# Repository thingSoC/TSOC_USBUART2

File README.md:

# TSOC_USBUART2

The thingSoC USBUART2 Base board incorporates a Cypress CY7C65215 Dual Channel USB Bridge, that supports UART, I2C, SPI, and JTAG interfaces in a thingSoC format.

The thingSoC USBUART2 Base board has two USB bridge channels, which can be programmed to be either UART, I2C, SPI, JTAG, or Capacitance Sensing (buttons/sliders) Human Input devices.

USB Bridge One (Port 1) is connected to an FTDI pinout compatible programming connector, while USB Bridge Two (Port 2) is connected to the thingSoC standard UART channel.

Port1 can be used to program a target microprocessor, at the same time Port2 is used for another purpose (i.e. debug channel, USB to RS-485 bridge, etc).  

It's like having two (2) FTDI adapters in One!

[ 
TSOC_USBUART2](https://github.com/thingSoC/TSOC_USBUART2)

The thingSoC Digital Programming Connector (DPC) is backward compatible with 
the industry standard six (6) pin "FTDI" pinout USB to Serial Adapter pinout.
However, the thingSoC Digital Programming Connector (DPC) includes 
two(2) extra pins (RTS & DEBUG) for extended device programming, 
such as "NodeMCU types" which use the RTS signal as a programming Enable,
and the DTR signal as a programming Reset.

---------------------------------------
## Use it as a Programming Dongle

[ 
TSOC_USBUART2 to FTDI Six (6) Pin : Programming an Arduino Pro](https://github.com/thingSoC/TSOC_USBUART2)

[ 
Programming a TSOC_NeoLED Board](https://github.com/thingSoC/TSOC_USBUART2)

[ 
Programming a TSOC_RS485 Board](https://github.com/thingSoC/TSOC_USBUART2)

---------------------------------------
## Use it as a Protocol Adapter

[ 
USB to WiFi Adapter](https://github.com/thingSoC/TSOC_USBUART2)

[ 
USB to RS-485 Adapter](https://github.com/thingSoC/TSOC_USBUART2)

[ 
USB to RS-232 Adapter](https://github.com/thingSoC/TSOC_USBUART2)

---------------------------------------
## TSOC_USBUART2 Model Images

[ 
TSOC_USBUART2](https://github.com/thingSoC/TSOC_USBUART2)

[ 
TSOC_USBUART2](https://github.com/thingSoC/TSOC_USBUART2)

---------------------------------------

## TSOC_USBUART2 Status <a name="TSOC_USBUART2_status"/>

Revision 1.0 - New Layout with Dual USB to UART device

Revision 2.0 - New PCB Outline, update to thingSoC Revision 2.0 

Revision 4.0 - New DPC connector, fix spacing.

Revision 4.1 - Update silkscreen, add more legends

---------------------------------------

## TSOC_USBUART2 Documentation Index <a name="TSOC_USBUART2_documentation_index"/>

[TSOC_USBUART2 Project](https://github.com/thingSoC/TSOC_USBUART2/)

[TSOC_USBUART2 Hardware](https://github.com/thingSoC/TSOC_USBUART2/tree/master/TSOC_USBUART2/hardware)

---------------------------------------

## thingSoC Documentation Index <a name="thingSoC_documentation_index"/>

[thingSoC Organization Website](http://thingSoC.github.io)

[thingSoC FAQ - Frequently Asked Questions](http://thingsoc.github.io/support/faq.html)

---------------------------------------

[ 
*thingSoC*](http://thingsoc.github.io)

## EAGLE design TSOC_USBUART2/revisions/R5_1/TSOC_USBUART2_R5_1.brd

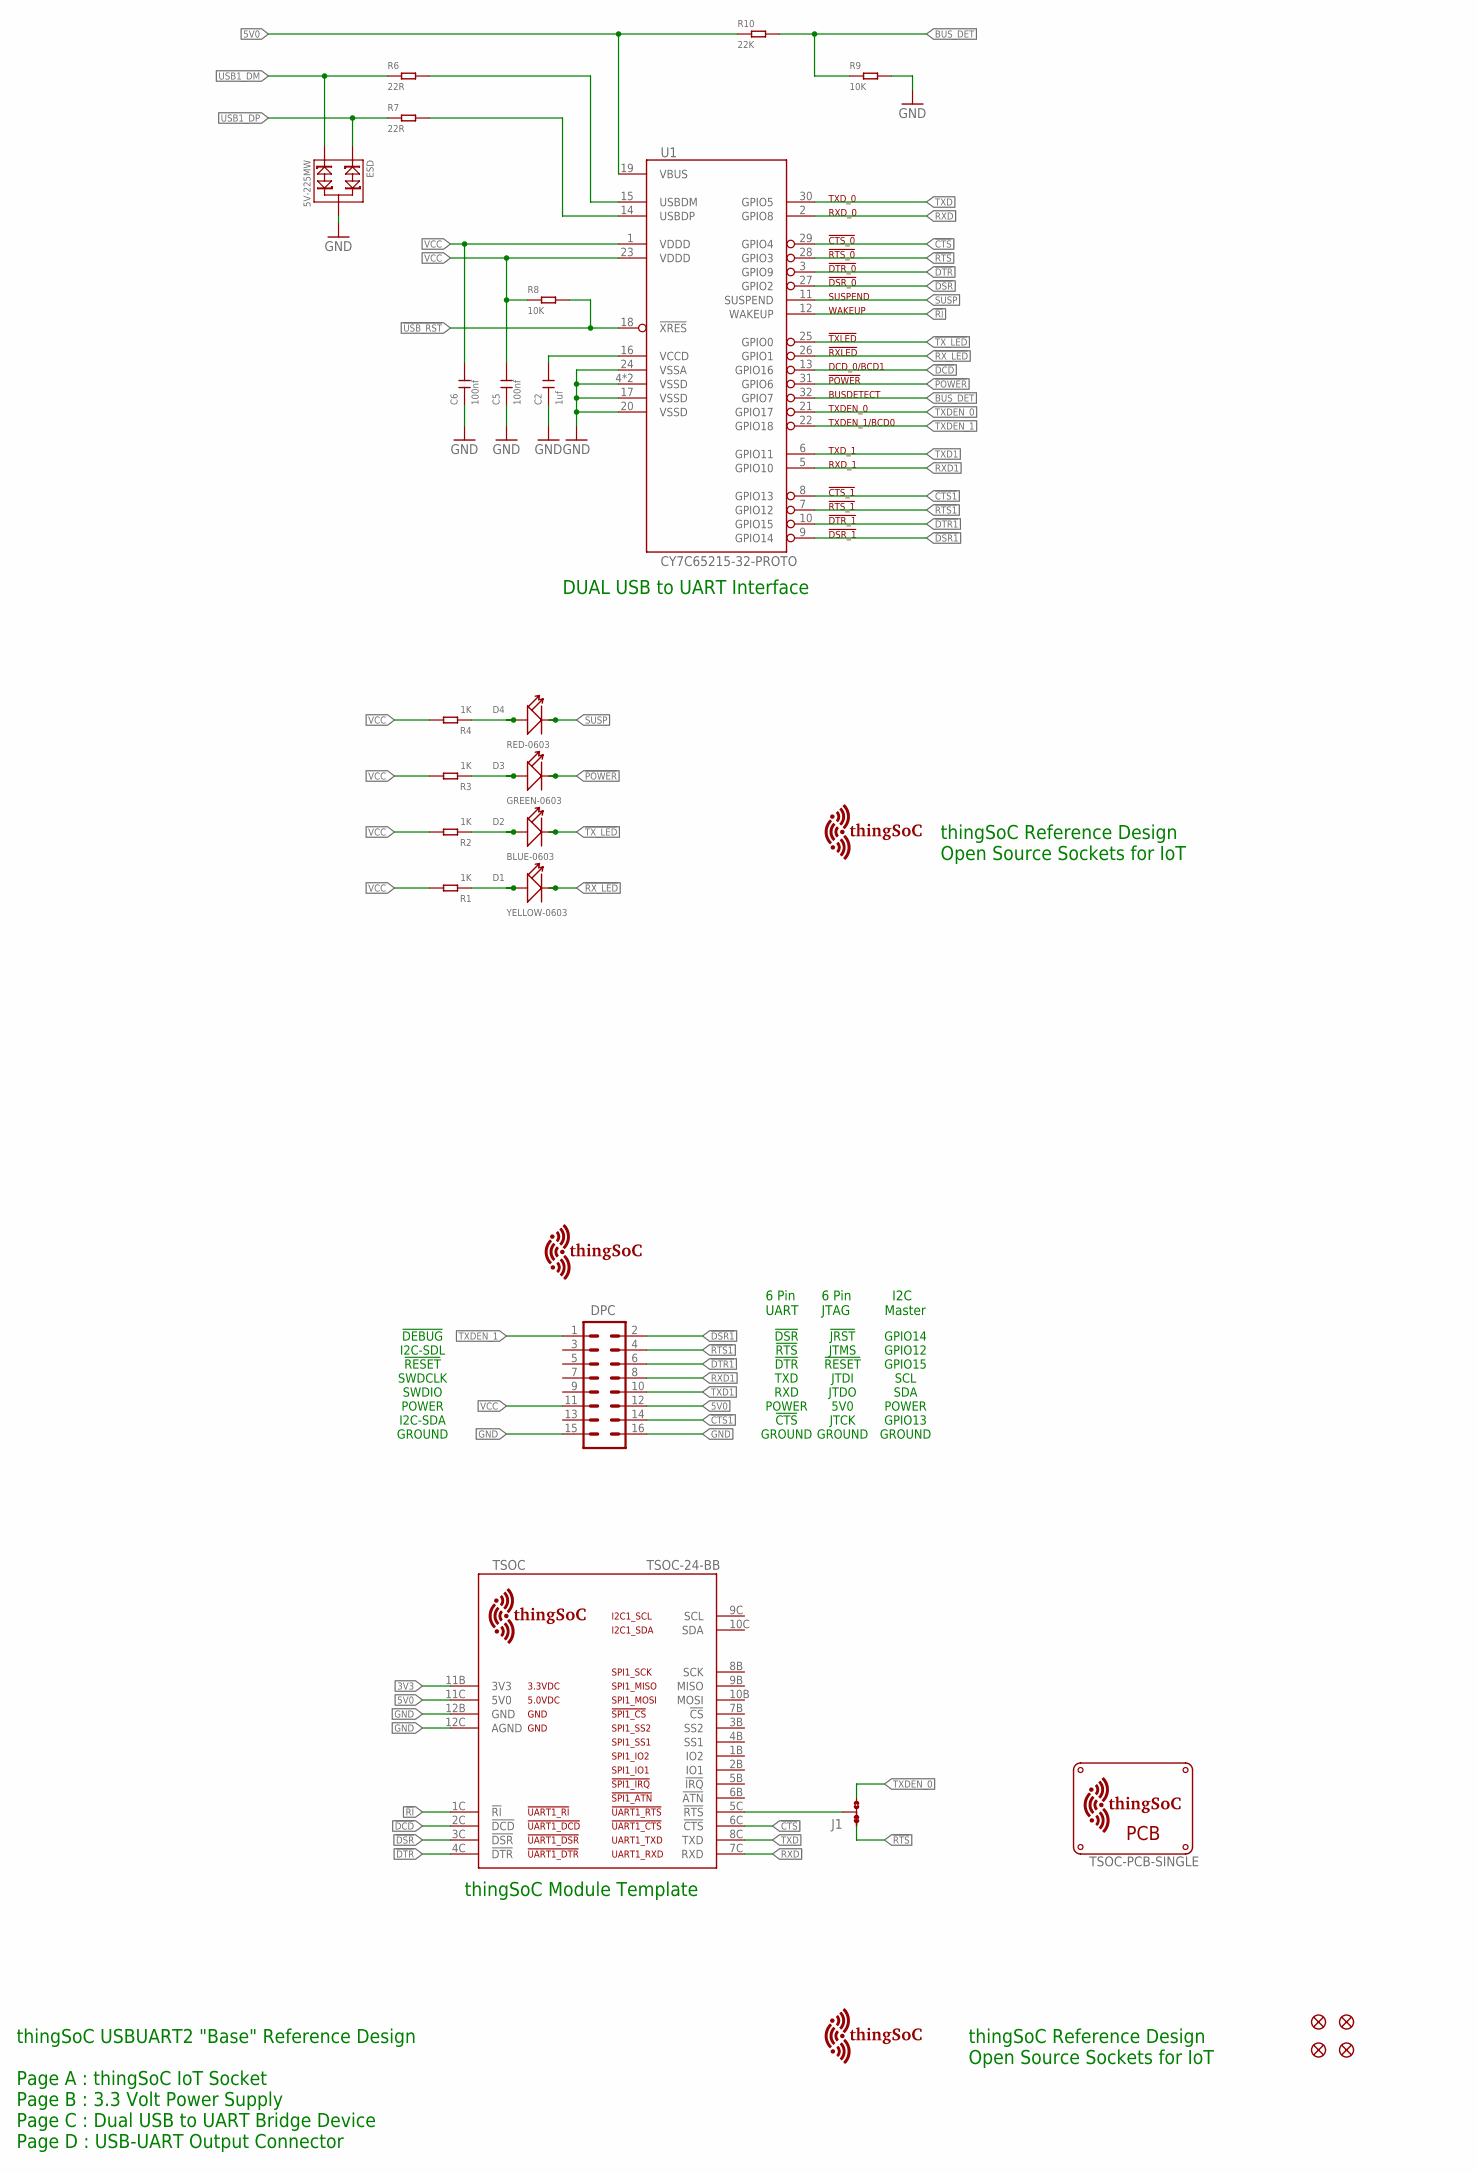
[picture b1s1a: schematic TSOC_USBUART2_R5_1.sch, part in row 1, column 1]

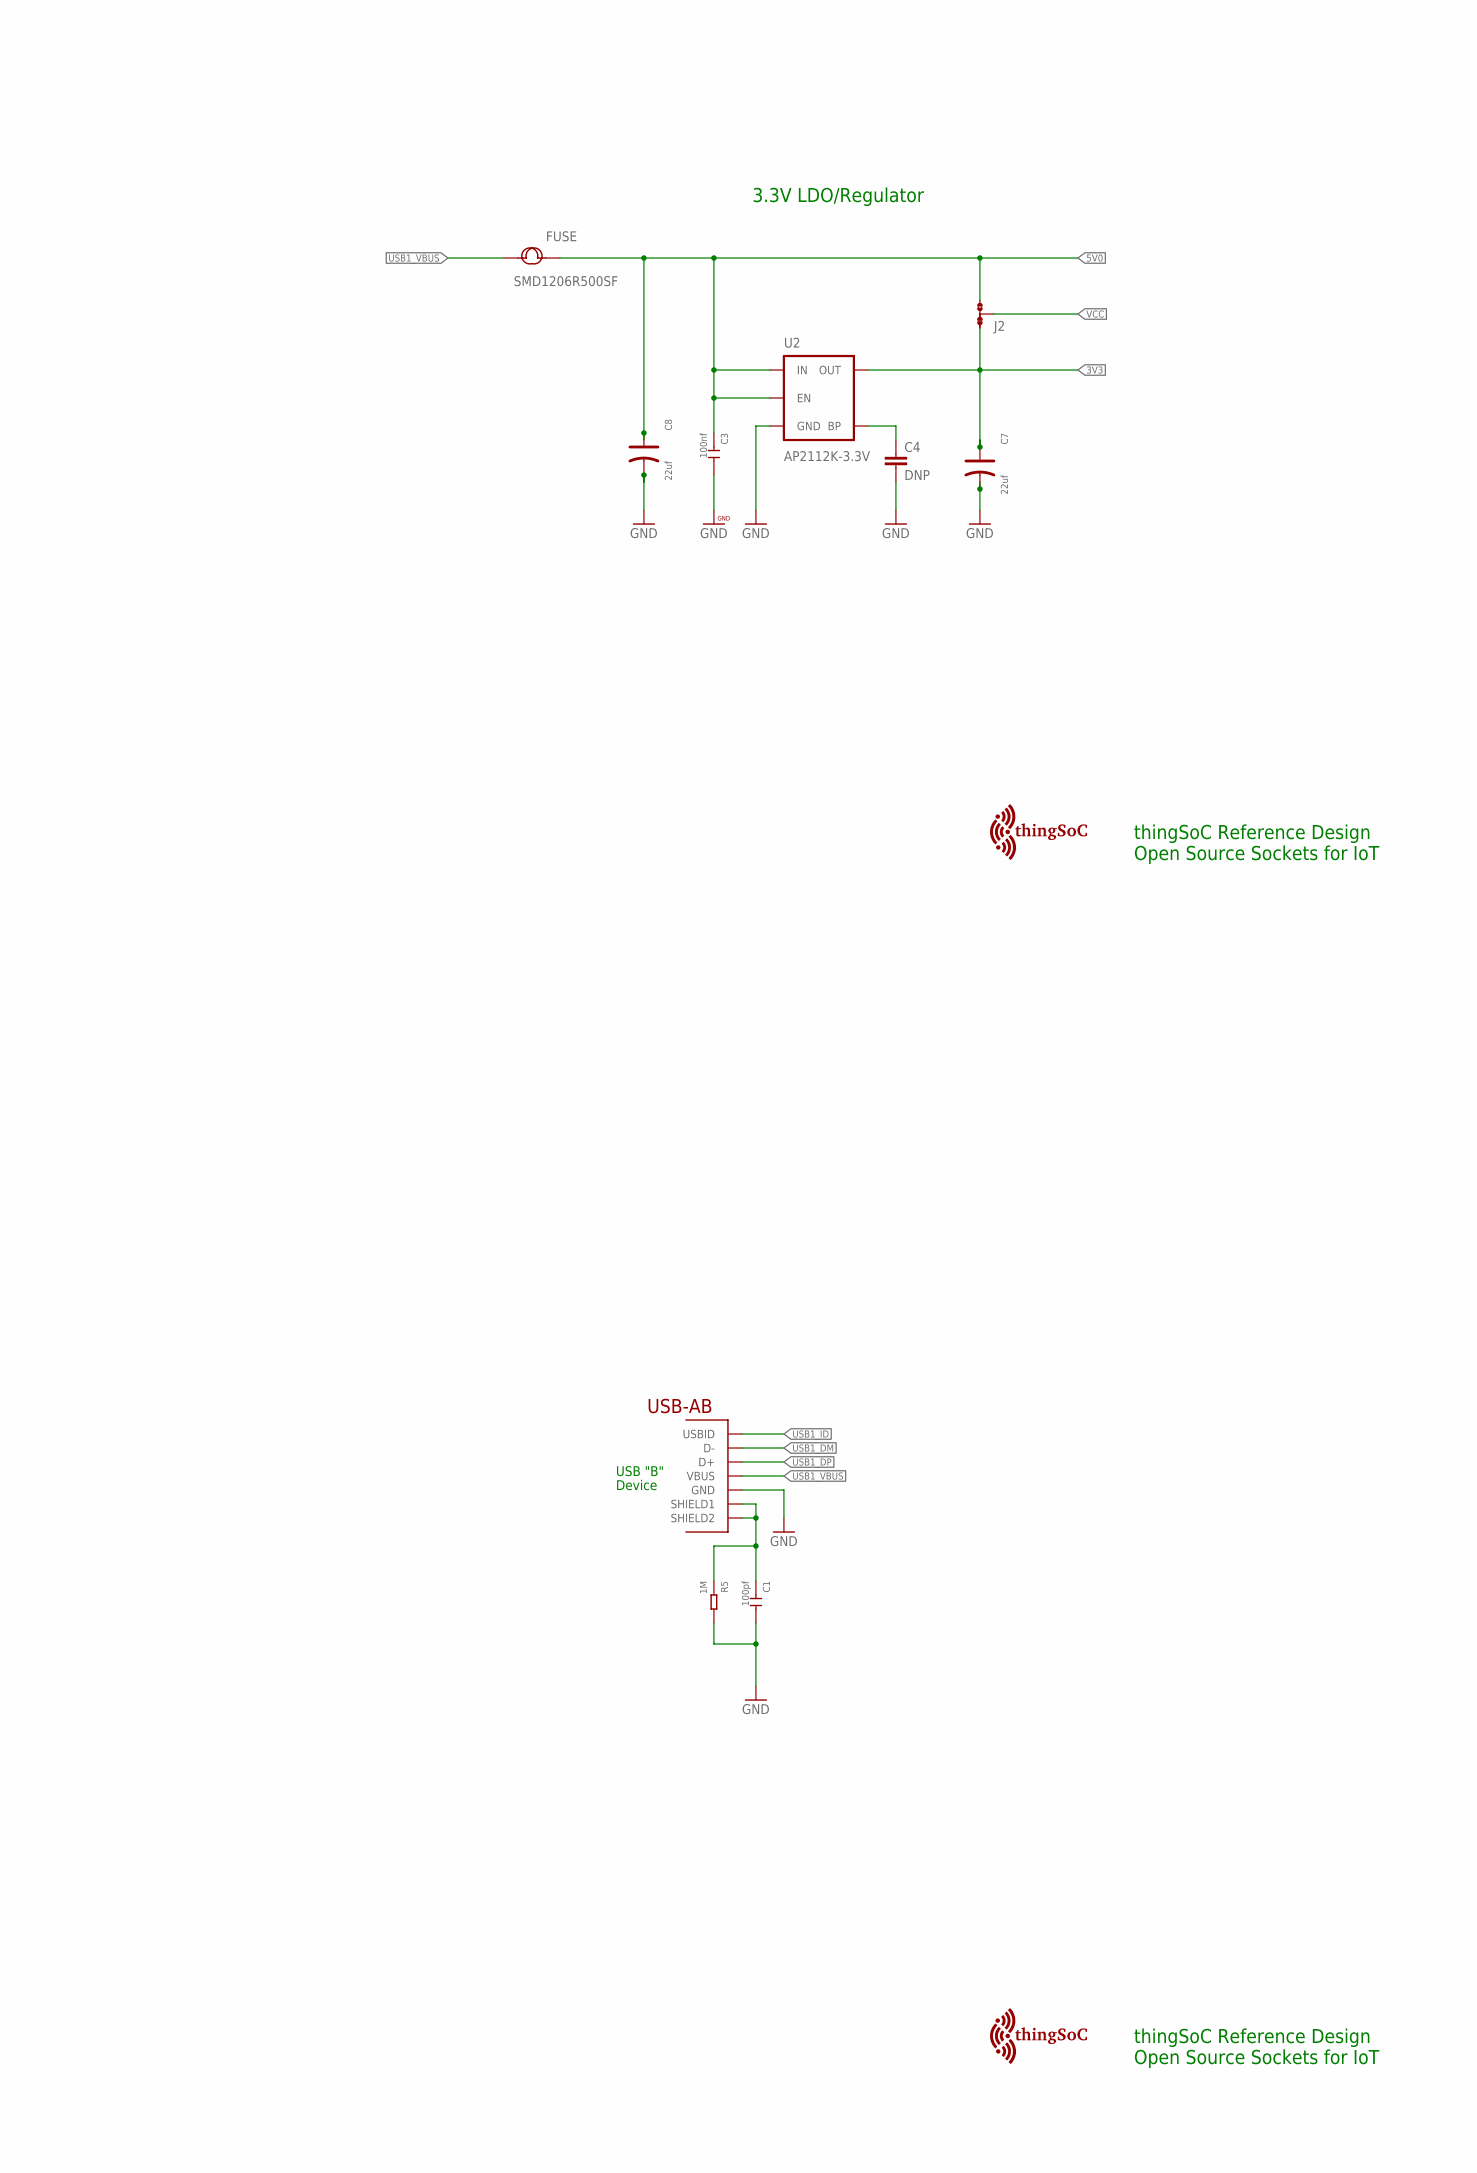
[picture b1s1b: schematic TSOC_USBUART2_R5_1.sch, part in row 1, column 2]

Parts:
$$U$2: TSOC-LOGO; TSOC-LOGO-BLANK
C1: 100pf; C0603
C2: 1uf; C0603
C3, C5, C6: 100nf; C0603
C4: DNP; EIA-0603
C7, C8: 22uf; AVX-A
D1: YELLOW-0603; LED-0603
D2: BLUE-0603; LED-0603
D3: GREEN-0603; LED-0603
D4: RED-0603; LED-0603
DPC: M08X2; 2X8
ESD: 5V-225MW; SOT-23
FID1, FID2, FID3, FID4: FIDUCIALUFIDUCIAL; MICRO-FIDUCIAL
FUSE: SMD1206R500SF; F1206
J1, J2: JMP-3-1_2
R1, R2, R3, R4: 1K; R0603
R5: 1M; R0603
R6, R7: 22R; R0603
R8, R9: 10K; R0603
R10: 22K; R0603
TSOC: TSOC-24-BB; TSOC-BB-S24
U1: CY7C65215-32-PROTO; QFN32-PROTO
U2: AP2112K-3.3V; SOT23-5
U$1, U$3: TSOC-LOGO; TSOC-LOGO-BLANK
U$4: TSOC-PCB-SINGLE; TSOC-BB-BRD-DIM
U$7: TSOC-LOGO-SMALL; TSOC-LOGO-SML
U$100: TSOC-LOGO-LRG
USB: USB_AB; USB-AB-MICRO-SMD

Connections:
3V3: C7.+, J2.1, TSOC.11B (3V3), U2.5 (OUT)
5V0: C3.1, C8.+, DPC.12, FUSE.2, J2.3, R10.1, TSOC.11C (5V0), U1.19 (VBUS), U2.1 (IN), U2.3 (EN)
!CTS: TSOC.6C (!CTS), U1.29 (GPIO4)
!CTS1: DPC.14, U1.8 (GPIO13)
!DCD: TSOC.2C (!DCD), U1.13 (GPIO16)
!DSR: TSOC.3C (!DSR), U1.27 (GPIO2)
!DSR1: DPC.2, U1.9 (GPIO14)
!DTR: TSOC.4C (!DTR), U1.3 (GPIO9)
!DTR1: DPC.6, U1.10 (GPIO15)
!POWER: D3.-, U1.31 (GPIO6)
!RI: TSOC.1C (!RI), U1.12 (WAKEUP)
!RTS: J1.1, U1.28 (GPIO3)
!RTS1: DPC.4, U1.7 (GPIO12)
!RX_LED: D1.-, U1.26 (GPIO1)
!TX_LED: D2.-, U1.25 (GPIO0)
!USB_RST: R8.2, U1.18 (!XRES)
BLU: D2.+, R2.1
BUS_DET: R9.1, R10.2, U1.32 (GPIO7)
BYPASS1: C4.1, U2.4 (BP)
GND: C1.2, C2.1, C3.2, C4.2, C5.1, C6.1, C7.-, C8.-, DPC.15, DPC.16, ESD.3, R5.2, R9.2, TSOC.12B (GND), TSOC.12C (AGND), U1.4 (VSSD), U1.17 (VSSD), U1.20 (VSSD), U1.24 (VSSA), U1.EXP (VSSD), U2.2 (GND), USB.GND
GRN: D3.+, R3.1
unnamed: J1.2, TSOC.5C (!RTS)
RED: D4.+, R4.1
RXD: TSOC.7C (RXD), U1.2 (GPIO8)
RXD1: DPC.8, U1.5 (GPIO10)
SUSP: D4.-, U1.11 (SUSPEND)
TXD: TSOC.8C (TXD), U1.30 (GPIO5)
TXD1: DPC.10, U1.6 (GPIO11)
TXDEN_0: J1.3, U1.21 (GPIO17)
TXDEN_1: DPC.1, U1.22 (GPIO18)
USB1_DM: ESD.2, R6.1, USB.D-
USB1_DP: ESD.1, R7.1, USB.D+
USB1_ID: USB.ID (USBID)
USB1_M: R6.2, U1.15 (USBDM)
USB1_P: R7.2, U1.14 (USBDP)
USB1_SHIELD: C1.1, R5.1, USB.SHIELD1, USB.SHIELD2
USB1_VBUS: FUSE.1, USB.VBUS
VCC: C5.2, C6.2, DPC.11, J2.2, R1.2, R2.2, R3.2, R4.2, R8.1, U1.1 (VDDD), U1.23 (VDDD)
VCCD1: C2.2, U1.16 (VCCD)
YEL: D1.+, R1.1

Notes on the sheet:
thingSoC Reference Design Open Source Sockets for IoT
USB "B"
Device
thingSoC USBUART2 "Base" Reference Design Page A : thingSoC IoT Socket Page B : 3.3 Volt Power Supply Page C : Dual USB to UART Bridge Device Page D : USB-UART Output Connector
DUAL USB to UART Interface
thingSoC Module Template
3.3V LDO/Regulator
I2C-SDA
I2C-SDL
!RESET
SWDCLK
SWDIO
POWER
GROUND
!DEBUG
!DSR
!RTS
!CTS
!DTR
TXD
RXD
!JRST
JTMS
JTCK
JTDI
JTDO
5V0
6 Pin UART
6 Pin JTAG
I2C Master
GPIO14
GPIO12
GPIO13
GPIO15
SCL
SDA

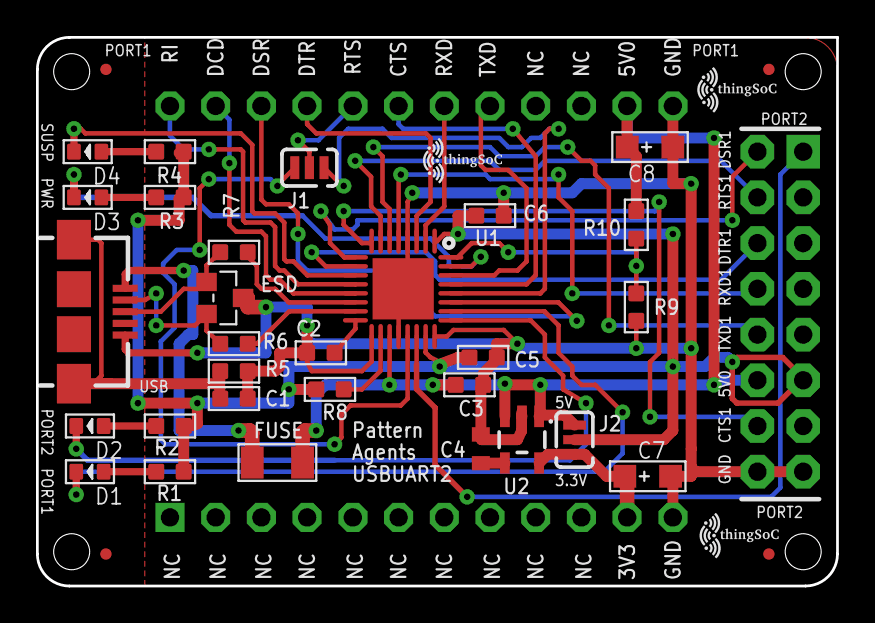
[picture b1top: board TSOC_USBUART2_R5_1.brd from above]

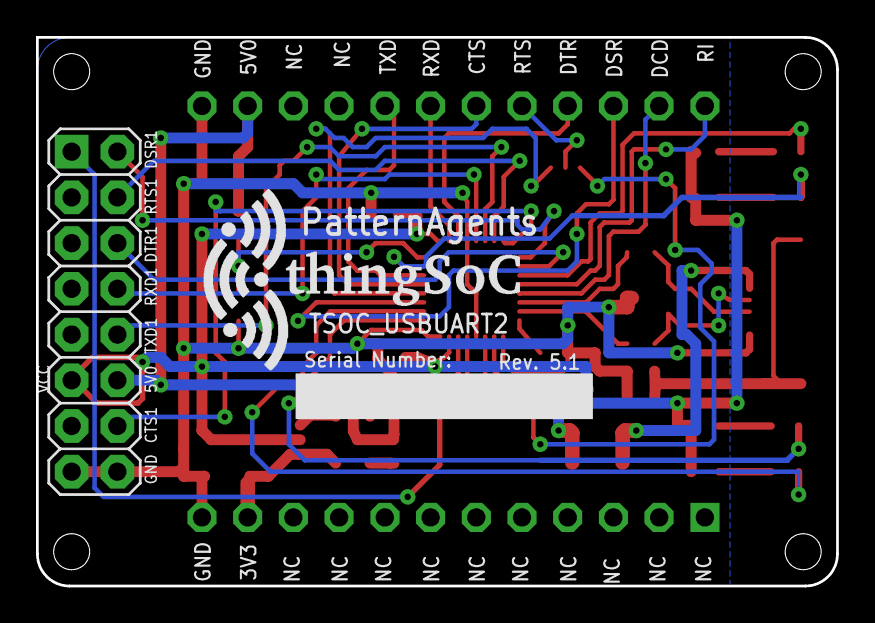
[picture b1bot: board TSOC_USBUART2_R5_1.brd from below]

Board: 2 copper layers, 44.5 x 30.5 mm, 43 parts (2 on the bottom side), 39 nets.

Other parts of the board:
U$5, U$6: TSOC-LOGO-SMALL; TSOC-LOGO-SML

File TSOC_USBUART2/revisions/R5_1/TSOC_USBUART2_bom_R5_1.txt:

Partlist exported from U:/PatternAgents/eagle/TSOC_Modules/TSOC_USBUART2/TSOC_USBUART2/revisions/R5_1/TSOC_USBUART2_R5_1.sch at 12/27/2016 11:35:59 AM

Qty Value              Device                          Package          Parts                  Description                                                                                                   
1   100pf              CERAMIC-100PF-50V-5%-NPO(0603)  C0603            C1                     302010076                                                                                                     
1   1uf                CERAMIC-1UF-25V-10%-X7R(0603)   C0603            C2                     302010139                                                                                                     
1   DNP                CAP-0603                        EIA-0603         C4                     Ceramic Capacitor SMD                                                                                         
3   100nf              CERAMIC-100NF-50V-10%-X7R(0603) C0603            C3, C5, C6             302010138                                                                                                     
2   22uf               TANTALUM-SMD-22UF-10V(AVX-A)    AVX-A            C7, C8                 302020008                                                                                                     
4   1K                 SMD-RES-1K-1%-1/10W(0603)       R0603            R1, R2, R3, R4         301010298                                                                                                     
1   1M                 SMD-RES-1M-1%-1/10W(0603)       R0603            R5                     301010151                                                                                                     
2   22R                SMD-RES-22R-5%-1/10W(0603)      R0603            R6, R7                 301010289                                                                                                     
2   10K                SMD-RES-10K-1%-1/10W(0603)      R0603            R8, R9                 301010299                                                                                                     
1   22K                SMD-RES-22K-5%-1/10W(0603)      R0603            R10                    301010132                                                                                                     
1   5V-225MW           SMD-DIODE-TVS-5V-225MW(SOT-23)  SOT-23           ESD                    304050003                                                                                                     
1   AP2112K-3.3V       V_REG_LDOSMD                    SOT23-5          U3                     Voltage Regulator LDO                                                                                         
1   BLUE-0603          SMD-LED-CLEAR-BLUE(0603)        LED-0603         D2                     304090045                                                                                                     
1   CY7C65215-32-PROTO CY7C65215-32-PROTO              QFN32-PROTO      U1                     Cypress EZ-USB ® CY7C65215-32QFN DUAL CHANNEL USB TO UART/SPI/IC Bridge                                       
1   GREEN-0603         SMD-LED-CLEAR-GREEN(0603)       LED-0603         D3                     304090043                                                                                                     
1   RED-0603           LED-SMD-RED-DIFFUSED(0603)      LED-0603         D4                     304090042                                                                                                     
1   SMD1206R500SF      SMD-PPTC-500MA(1206)            F1206            FUSE                   307010002                                                                                                     
1   USB_AB             USB_AB                          USB-AB-MICRO-SMD USB                     
1   YELLOW-0603        SMD-LED-CLEAR-YELLOW(0603)      LED-0603         D1                     304090044

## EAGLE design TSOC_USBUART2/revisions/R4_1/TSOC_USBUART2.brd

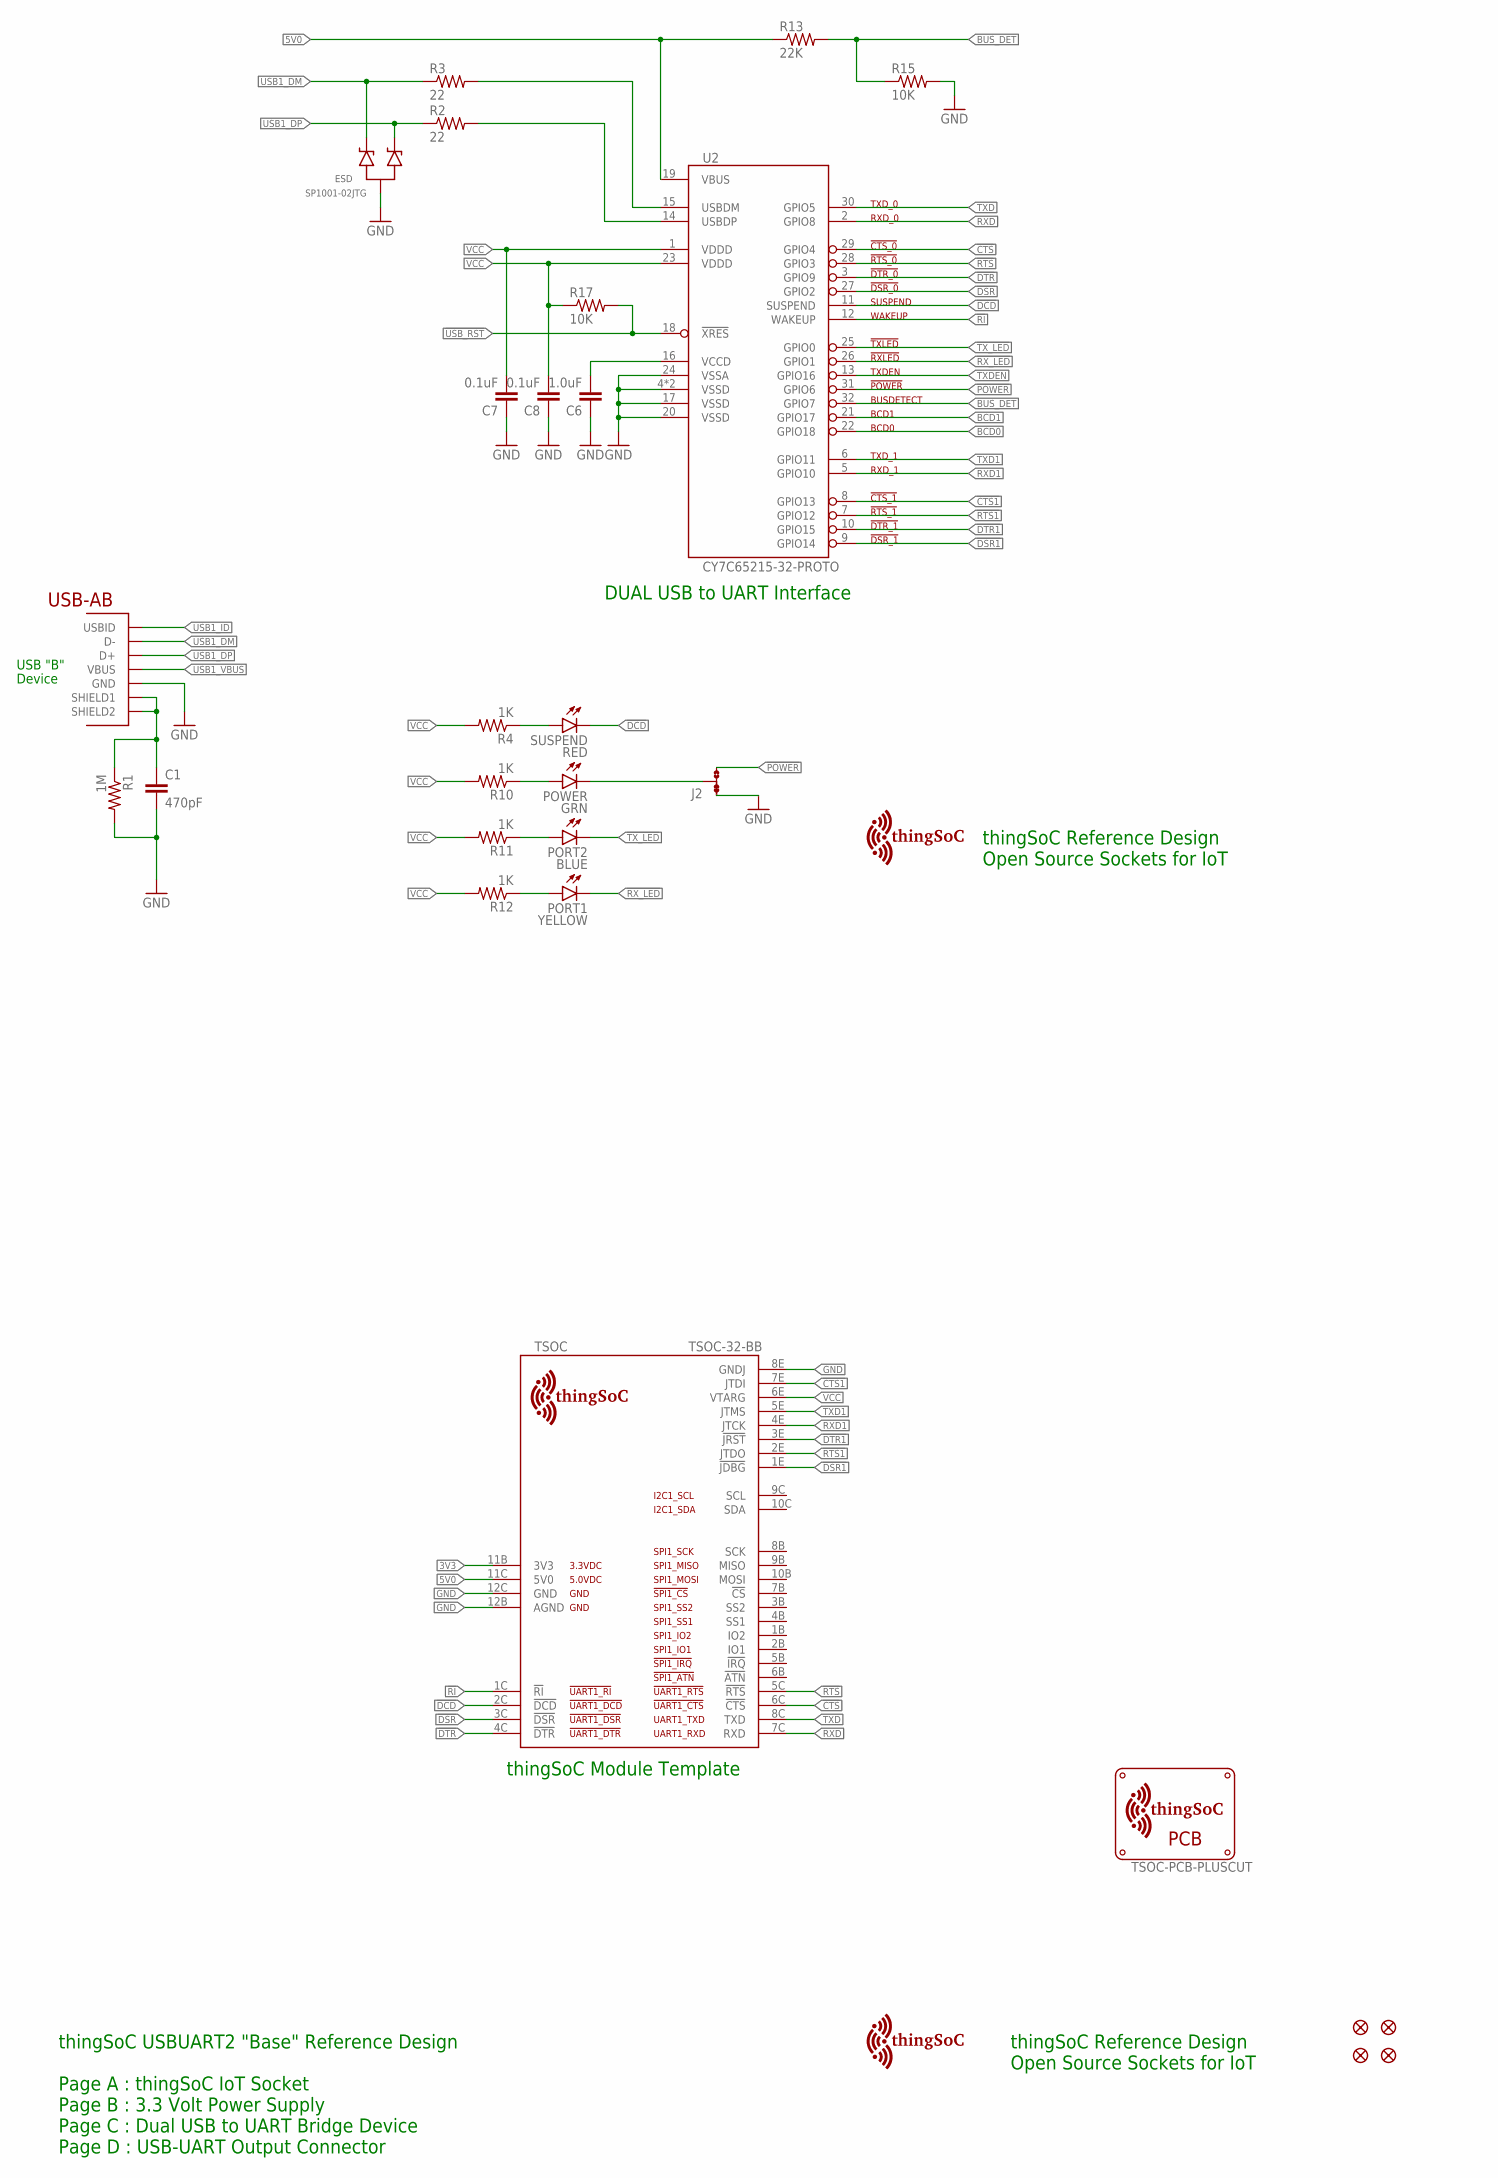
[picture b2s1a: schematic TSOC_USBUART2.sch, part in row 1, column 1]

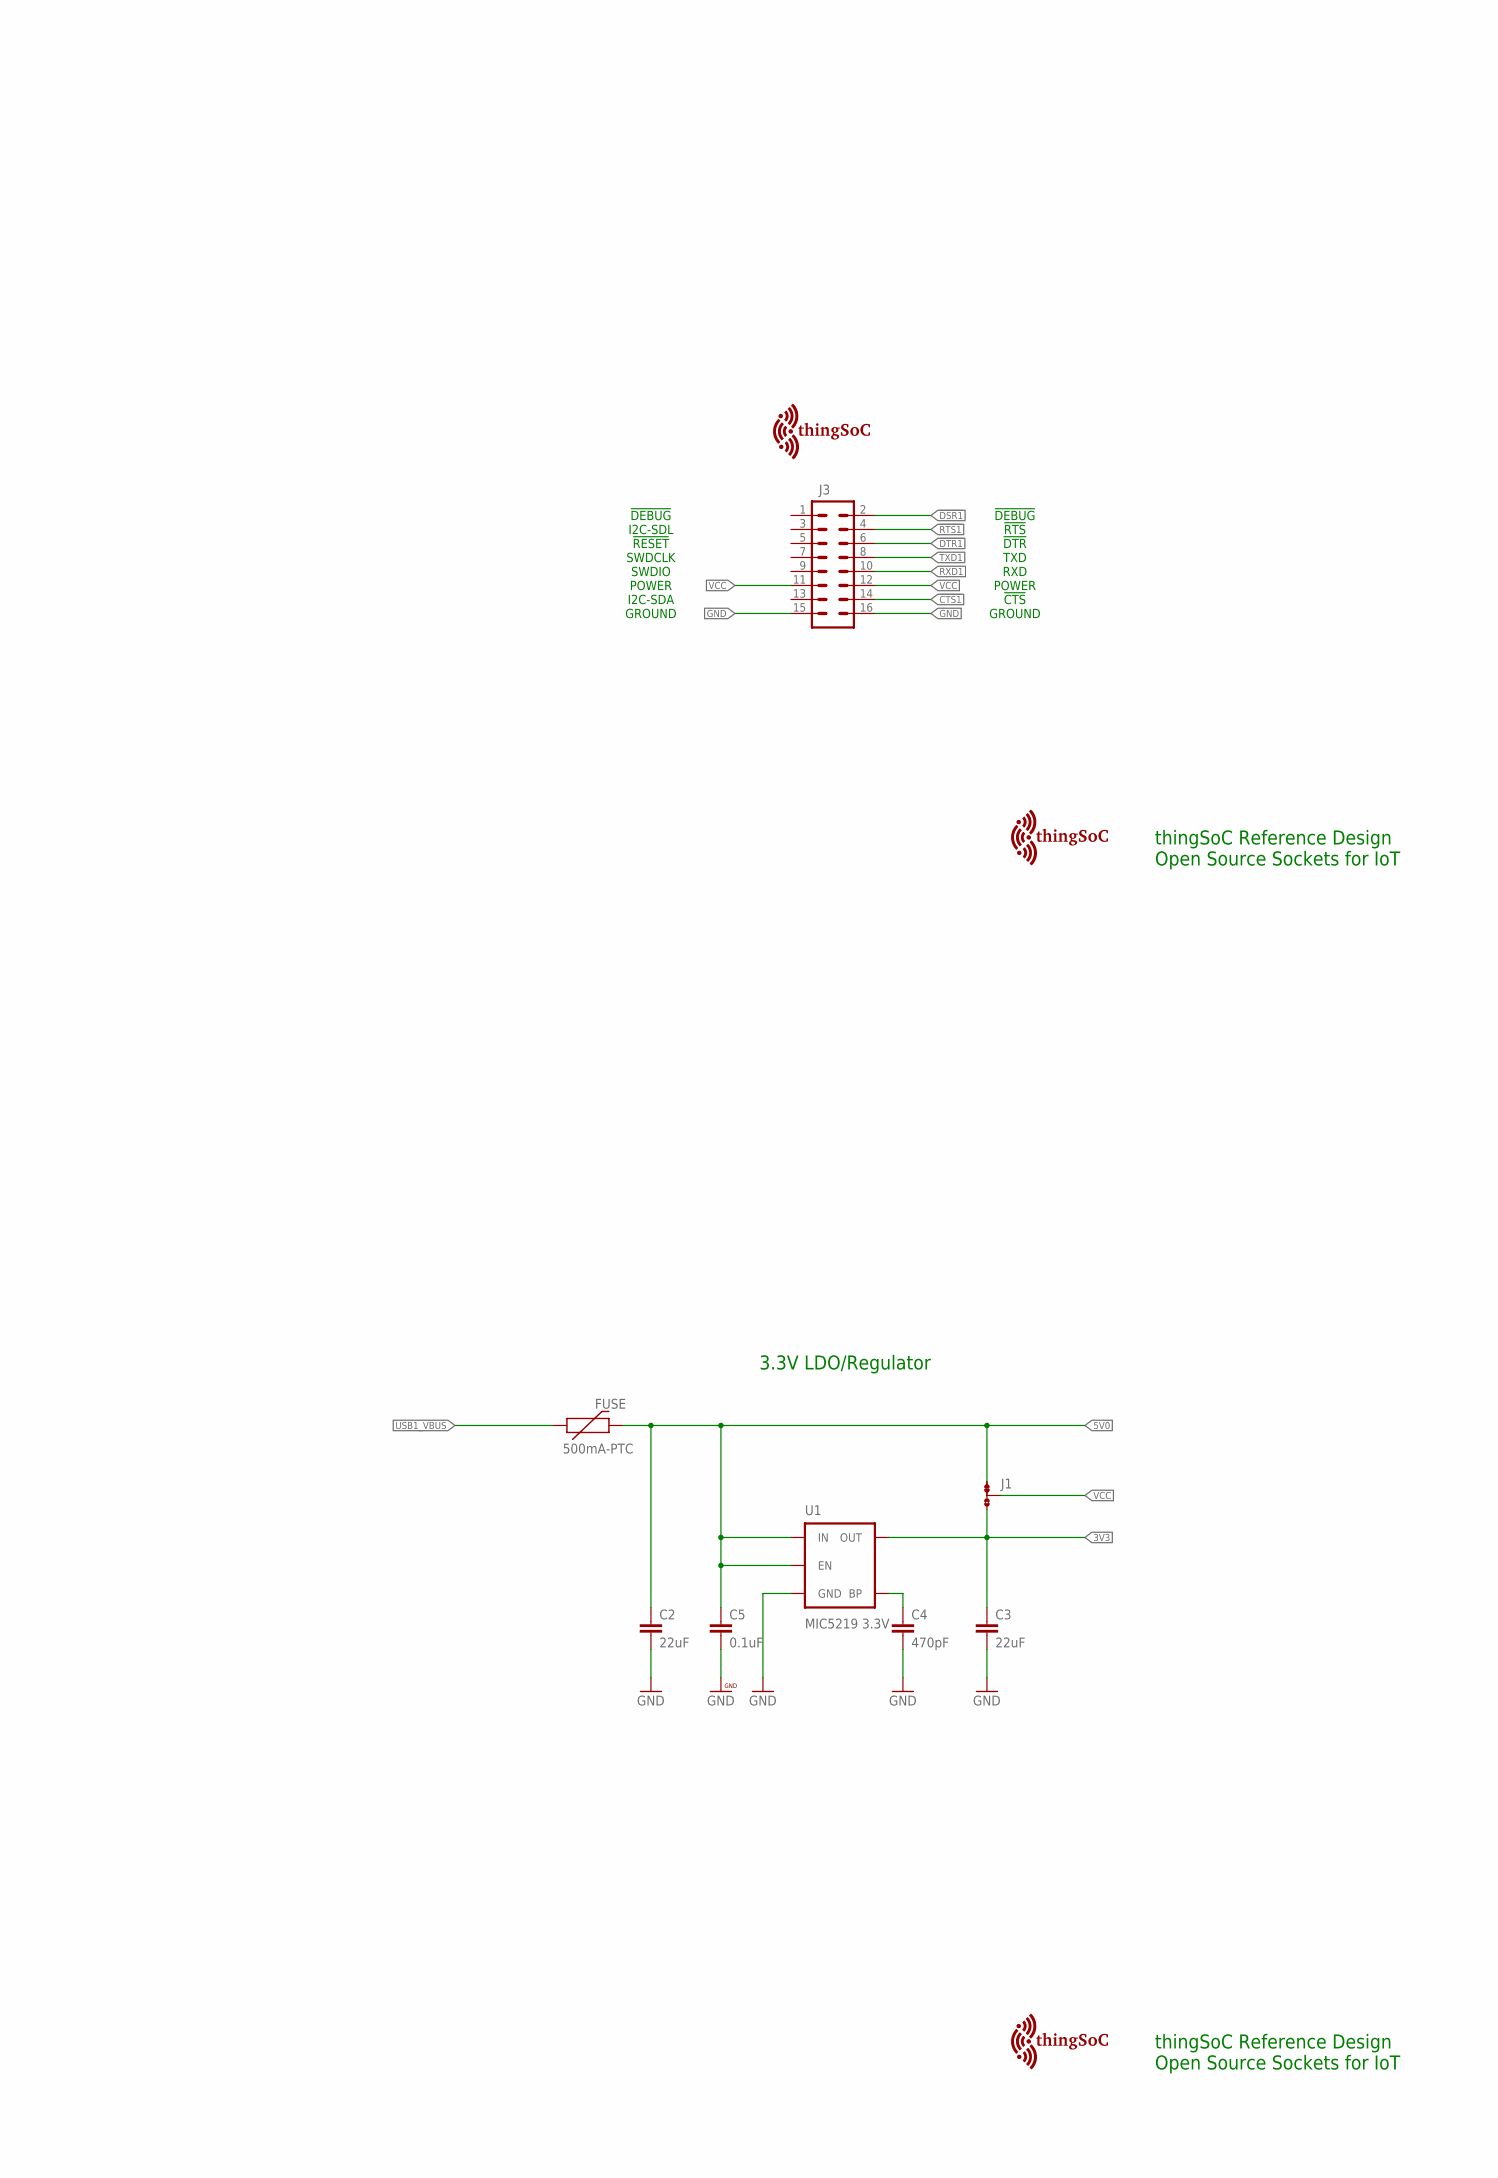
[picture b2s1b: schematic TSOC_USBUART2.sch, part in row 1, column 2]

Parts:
C1, C4: 470pF; EIA-0603
C2, C3: 22uF; EIA-1206
C5, C7, C8: 0.1uF; EIA-0603
C6: 1.0uF; EIA-0603
ESD: SP1001-02JTG; SC70-3
FID1, FID2, FID3, FID4: FIDUCIALUFIDUCIAL; MICRO-FIDUCIAL
FUSE: 500mA-PTC; PTC-1206
J1, J2: JMP-3-1_2
J3: M08X2; 2X8
PORT1: YELLOW; LED-0603
PORT2: BLUE; LED-0603
POWER: GRN; LED-0603
R1: 1M; EIA-0603
R2, R3: 22; EIA-0603
R4, R10, R11, R12: 1K; EIA-0603
R13: 22K; EIA-0603
R15, R17: 10K; EIA-0603
SUSPEND: RED; LED-0603
TSOC: TSOC-32-BB; TSOC-BB-S32
U1: MIC5219 3.3V; SOT23-5
U2: CY7C65215-32-PROTO; QFN32-PROTO
U$3: TSOC-LOGO-LRG
U$4, U$5, U$6: TSOC-LOGO; TSOC-LOGO-BLANK
U$7: TSOC-PCB-PLUSCUT; TSOC-BB-BRD-PLUS-CUT
U$8: TSOC-LOGO-SMALL; TSOC-LOGO-SML
USB: USB_AB; USB-AB-MICRO-SMD

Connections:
3V3: C3.1, J1.3, TSOC.11B (3V3), U1.5 (OUT)
5V0: C2.1, C5.1, FUSE.2, J1.1, R13.1, TSOC.11C (5V0), U1.1 (IN), U1.3 (EN), U2.19 (VBUS)
!CTS: TSOC.6C (!CTS), U2.29 (GPIO4)
!CTS1: J3.14, TSOC.7E (JTDI), U2.8 (GPIO13)
!DCD: SUSPEND.C, TSOC.2C (!DCD), U2.11 (SUSPEND)
!DSR: TSOC.3C (!DSR), U2.27 (GPIO2)
!DSR1: J3.2, TSOC.1E (!JDBG), U2.9 (GPIO14)
!DTR: TSOC.4C (!DTR), U2.3 (GPIO9)
!DTR1: J3.6, TSOC.3E (!JRST), U2.10 (GPIO15)
!POWER: J2.3, U2.31 (GPIO6)
!RI: TSOC.1C (!RI), U2.12 (WAKEUP)
!RTS: TSOC.5C (!RTS), U2.28 (GPIO3)
!RTS1: J3.4, TSOC.2E (JTDO), U2.7 (GPIO12)
!RX_LED: PORT1.C, U2.26 (GPIO1)
!TX_LED: PORT2.C, U2.25 (GPIO0)
!USB_RST: R17.2, U2.18 (!XRES)
BCD0: U2.22 (GPIO18)
BCD1: U2.21 (GPIO17)
BLU: PORT2.A, R11.1
BUS_DET: R13.2, R15.1, U2.32 (GPIO7)
BYPASS1: C4.1, U1.4 (BP)
GND: C1.2, C2.2, C3.2, C4.2, C5.2, C6.1, C7.1, C8.1, ESD.3 (A), J2.1, J3.15, J3.16, R1.2, R15.2, TSOC.8E (GNDJ), TSOC.12B (AGND), TSOC.12C (GND), U1.2 (GND), U2.4 (VSSD), U2.17 (VSSD), U2.20 (VSSD), U2.24 (VSSA), U2.EXP (VSSD), USB.GND
GRN: POWER.A, R10.1
PWR: J2.2, POWER.C
RED: R4.1, SUSPEND.A
RXD: TSOC.7C (RXD), U2.2 (GPIO8)
RXD1: J3.10, TSOC.4E (JTCK), U2.5 (GPIO10)
TXD: TSOC.8C (TXD), U2.30 (GPIO5)
TXD1: J3.8, TSOC.5E (JTMS), U2.6 (GPIO11)
TXDEN: U2.13 (GPIO16)
USB1_DM: ESD.2 (C2), R3.1, USB.D-
USB1_DP: ESD.1 (C1), R2.1, USB.D+
USB1_ID: USB.ID (USBID)
USB1_M: R3.2, U2.15 (USBDM)
USB1_P: R2.2, U2.14 (USBDP)
USB1_SHIELD: C1.1, R1.1, USB.SHIELD1, USB.SHIELD2
USB1_VBUS: FUSE.1, USB.VBUS
VCC: C7.2, C8.2, J1.2, J3.11, J3.12, R4.2, R10.2, R11.2, R12.2, R17.1, TSOC.6E (VTARG), U2.1 (VDDD), U2.23 (VDDD)
VCCD1: C6.2, U2.16 (VCCD)
YEL: PORT1.A, R12.1

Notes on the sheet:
thingSoC Reference Design Open Source Sockets for IoT
USB "B"
Device
thingSoC USBUART2 "Base" Reference Design Page A : thingSoC IoT Socket Page B : 3.3 Volt Power Supply Page C : Dual USB to UART Bridge Device Page D : USB-UART Output Connector
DUAL USB to UART Interface
thingSoC Module Template
3.3V LDO/Regulator
I2C-SDA
I2C-SDL
!RESET
SWDCLK
SWDIO
POWER
GROUND
!DEBUG
!RTS
!CTS
!DTR
TXD
RXD

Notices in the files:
parts and their libraries:
thingSoC: License : http://creativecommons.org/licenses/by-sa/4.0
(Creative Commons 4.0)
PatternAgents-Cypress: License : http://creativecommons.org/licenses/by-sa/3.0
(Creative Commons 3.0)
